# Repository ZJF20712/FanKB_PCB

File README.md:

# FanKB_PCB
The PCB project for FanKB
  Designed by KiCad.
    This is the third version,the next version I'd like to change MCU to stm32(software use Chibios), or make MDBT40 BT module on board to reduce the price of this keyboard.

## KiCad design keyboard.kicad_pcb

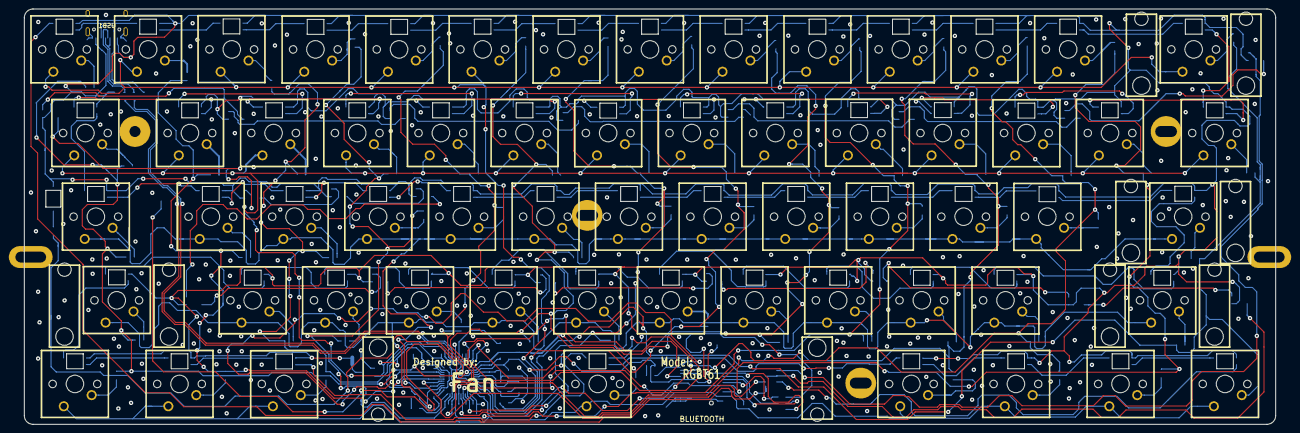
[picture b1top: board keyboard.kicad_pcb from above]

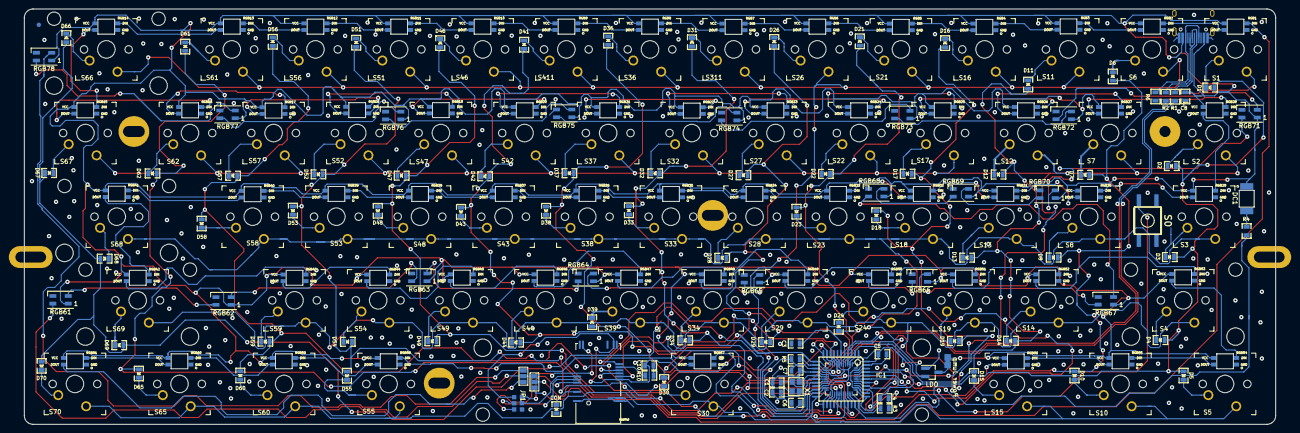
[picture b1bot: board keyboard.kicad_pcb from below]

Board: 2 copper layers, 285.0 x 94.6 mm, 245 parts (168 on the bottom side), 186 nets.

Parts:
BLUETOOTH: MDBT40; MDBT40_F
C1, C2: 22p; 0805C
C3, C8, C10: 1u; 0805C
C4, C5, C6, C7: 100n; 0805C
CON: LED; 0805D
D1, D2, D3, D4, D5, D6, D7, D8, D10, D11, D12, D13, D14, D15, D16, D17, D18, D19, D21, D22, D23, D24, D26, D27, D28, D29, D30, D31, D32, D33, D34, D36, D37, D38, D39, D41, D42, D43, D44, D46, D47, D48, D49, D51, D52, D53, D54, D55, D56, D57, D58, D59, D60, D61, D62, D65, D66, D67, D68, D69, D70: 1N4148; 0805D
DC1: LED; 3528_LED
FID: FIDUCIAL
HOLE: VAL**; PKRHSL
HOLE#2: VAL**; PKRHSL
HOLE#3, HOLE#4, HOLE#5: VAL**; PKRH
HOLE#6: VAL**; PKRHC
IC1: ATMEGA32U4; TQFP44
JP1, JP2: JUMPER3; SolderJumper-3_P1.3mm_Open_Pad1.0x1.5mm_NumberLabels
LDO: 2N7002; SOT-23_Handsoldering
MXST: VAL**; MXST
MXST#2, MXST#3, MXST#4, MXST#5, MXST#6, MXST#7, MXST#8, MXST#9, MXST#10: VAL**; MXST
P2: CONN_3X2; Jumper-UserFriendly
R1, R2: 22; 0805R
R3, R5: 10k; 0805R
R4: 300; 0805R
R6: 5.1K; 0805R
R10: 10K; 0805R
RGB1, RGB2, RGB3, RGB4, RGB5, RGB6, RGB7, RGB8, RGB9, RGB10, RGB11, RGB12, RGB13, RGB14, RGB15, RGB16, RGB17, RGB18, RGB19, RGB20, RGB21, RGB22, RGB23, RGB24, RGB25, RGB26, RGB27, RGB28, RGB29, RGB30, RGB31, RGB32, RGB33, RGB34, RGB35, RGB36, RGB37, RGB38, RGB39, RGB40, RGB41, RGB42, RGB43, RGB44, RGB45, RGB46, RGB47, RGB48, RGB49, RGB50, RGB51, RGB52, RGB53, RGB54, RGB55, RGB56, RGB57, RGB58, RGB59, RGB60, RGB81: WS2812B; WS2812-3528-with-sik
RGB61, RGB62, RGB63, RGB64, RGB65, RGB66, RGB67, RGB68, RGB69, RGB70, RGB71, RGB72, RGB73, RGB74, RGB75, RGB76, RGB77, RGB78: WS2812B; LED_SK6812MINI_PLCC4_3.5x3.5mm_P1.75mm
S0: DTSM-6; KSEM31GLFS
S1, S2, S3, S4, S5, S6, S7, S8, S10, S11, S12, S13, S14, S15, S16, S17, S18, S19, S21, S22, S23, S24, S26, S27, S28, S29, S30, S32, S33, S34, S36, S37, S38, S39, S42, S43, S44, S46, S47, S48, S49, S51, S52, S53, S54, S55, S56, S57, S58, S59, S60, S61, S62, S65, S66, S67, S68, S69, S70, S311, S411: MX1A; MX
USB1: HRO-TYPE-C-31-M-12; HRO-TYPE-C-31-M-12-HandSoldering
X1: ASX3F; 4-SMD

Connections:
/CONed: BLUETOOTH.39, CON.1
/D+: IC1.4, R2.1
/D-: IC1.3, R1.1
/DFU: BLUETOOTH.24, P2.5
/DIN_D: JP1.1, JP2.2, RGB61.4
/DIN_M: JP1.3, RGB1.4
/DIO_RST: BLUETOOTH.35, P2.3
/DOUT_D: JP2.1, RGB78.2
/DOUT_M: JP2.3, RGB81.2
/FACRST: BLUETOOTH.34, P2.4
/MISO: BLUETOOTH.5, IC1.11
/MOSI: BLUETOOTH.6, IC1.10
/SCK: BLUETOOTH.4, IC1.9
/SWCLK: BLUETOOTH.36, P2.2
/WS2812: IC1.38, JP1.2
/caps: IC1.8, R4.2
/col1: D1.1, D2.1, D3.1, D4.1, D5.1, IC1.41
/col2: D6.1, D7.1, D8.1, D10.1, IC1.40
/col3: D11.1, D12.1, D13.1, D14.1, D15.1, IC1.1
/col4: D16.1, D17.1, D18.1, D19.1, IC1.32
/col5: D21.1, D22.1, D23.1, D24.1, IC1.31
/col6: D26.1, D27.1, D28.1, D29.1, D30.1, IC1.30
/col7: D31.1, D32.1, D33.1, D34.1, IC1.25
/col8: D36.1, D37.1, D38.1, D39.1, IC1.20
/col9: D41.1, D42.1, D43.1, D44.1, IC1.12
/col10: D46.1, D47.1, D48.1, D49.1, IC1.29
/col11: D51.1, D52.1, D53.1, D54.1, D55.1, IC1.28
/col12: D56.1, D57.1, D58.1, D59.1, D60.1, IC1.27
/col13: D61.1, D62.1, D65.1, IC1.26
/col14: D66.1, D67.1, D68.1, D69.1, D70.1, IC1.21
/row1: IC1.18, S1.1, S6.1, S11.1, S16.1, S21.1, S26.1, S36.1, S46.1, S51.1, S56.1, S61.1, S66.1, S311.1, S411.1
/row2: IC1.19, S2.1, S7.1, S12.1, S17.1, S22.1, S27.1, S32.1, S37.1, S42.1, S47.1, S52.1, S57.1, S62.1, S67.1
/row3: IC1.37, S3.1, S8.1, S13.1, S18.1, S23.1, S28.1, S33.1, S38.1, S43.1, S48.1, S53.1, S58.1, S68.1
/row4: IC1.36, S4.1, S14.1, S19.1, S24.1, S29.1, S34.1, S39.1, S44.1, S49.1, S54.1, S59.1, S69.1
/row5: IC1.22, S5.1, S10.1, S15.1, S30.1, S55.1, S60.1, S65.1, S70.1
GND: BLUETOOTH.1, BLUETOOTH.2, BLUETOOTH.13, BLUETOOTH.16, BLUETOOTH.25, BLUETOOTH.42, C1.2, C2.2, C3.2, C4.2, C5.2, C6.2, C7.2, C8.2, C10.1, CON.2, IC1.5, IC1.15, IC1.23, IC1.35, IC1.43, LDO.1, P2.6, R3.2, R6.1, R10.1, RGB1.3, RGB2.3, RGB3.3, RGB4.3, RGB5.3, RGB6.3, RGB7.3, RGB8.3, RGB9.3, RGB10.3, RGB11.3, RGB12.3, RGB13.3, RGB14.3, RGB15.3, RGB16.3, RGB17.3, RGB18.3, RGB19.3, RGB20.3, RGB21.3, RGB22.3, RGB23.3, RGB24.3, RGB25.3, RGB26.3, RGB27.3, RGB28.3, RGB29.3, RGB30.3, RGB31.3, RGB32.3, RGB33.3, RGB34.3, RGB35.3, RGB36.3, RGB37.3, RGB38.3, RGB39.3, RGB40.3, RGB41.3, RGB42.3, RGB43.3, RGB44.3, RGB45.3, RGB46.3, RGB47.3, RGB48.3, RGB49.3, RGB50.3, RGB51.3, RGB52.3, RGB53.3, RGB54.3, RGB55.3, RGB56.3, RGB57.3, RGB58.3, RGB59.3, RGB60.3, RGB61.3, RGB62.3, RGB63.3, RGB64.3, RGB65.3, RGB66.3, RGB67.3, RGB68.3, RGB69.3, RGB70.3, RGB71.3, RGB72.3, RGB73.3, RGB74.3, RGB75.3, RGB76.3, RGB77.3, RGB78.3, RGB81.3, S0.1, USB1.1, USB1.12, USB1.13, X1.2, X1.4
unnamed: C1.1, IC1.16, X1.1
unnamed: C2.1, IC1.17, X1.3
unnamed: C3.1, IC1.6
unnamed: D1.2, S1.2
unnamed: D2.2, S2.2
unnamed: D3.2, S3.2
unnamed: D4.2, S4.2
unnamed: D5.2, S5.2
unnamed: D6.2, S6.2
unnamed: D7.2, S7.2
unnamed: D8.2, S8.2
unnamed: D10.2, S10.2
unnamed: D11.2, S11.2
unnamed: D12.2, S12.2
unnamed: D13.2, S13.2
unnamed: D14.2, S14.2
unnamed: D15.2, S15.2
unnamed: D16.2, S16.2
unnamed: D17.2, S17.2
unnamed: D18.2, S18.2
unnamed: D19.2, S19.2
unnamed: D21.2, S21.2
unnamed: D22.2, S22.2
unnamed: D23.2, S23.2
unnamed: D24.2, S24.2
unnamed: D26.2, S26.2
unnamed: D27.2, S27.2
unnamed: D28.2, S28.2
unnamed: D29.2, S29.2
unnamed: D30.2, S30.2
unnamed: D31.2, S311.2
unnamed: D32.2, S32.2
unnamed: D33.2, S33.2
unnamed: D34.2, S34.2
unnamed: D36.2, S36.2
unnamed: D37.2, S37.2
unnamed: D38.2, S38.2
unnamed: D39.2, S39.2
unnamed: D41.2, S411.2
unnamed: D42.2, S42.2
unnamed: D43.2, S43.2
unnamed: D44.2, S44.2
unnamed: D46.2, S46.2
unnamed: D47.2, S47.2
unnamed: D48.2, S48.2
unnamed: D49.2, S49.2
unnamed: D51.2, S51.2
unnamed: D52.2, S52.2
unnamed: D53.2, S53.2
unnamed: D54.2, S54.2
unnamed: D55.2, S55.2
unnamed: D56.2, S56.2
unnamed: D57.2, S57.2
unnamed: D58.2, S58.2
unnamed: D59.2, S59.2
unnamed: D60.2, S60.2
unnamed: D61.2, S61.2
unnamed: D62.2, S62.2
unnamed: D65.2, S65.2
unnamed: D66.2, S66.2
unnamed: D67.2, S67.2
unnamed: D68.2, S68.2
unnamed: D69.2, S69.2
unnamed: D70.2, S70.2
unnamed: DC1.2, R4.1
unnamed: IC1.13, R5.2, S0.3
unnamed: IC1.33, R3.1
unnamed: BLUETOOTH.8, IC1.39
unnamed: R1.2, USB1.5, USB1.7
unnamed: R2.2, USB1.6, USB1.8
unnamed: R6.2, USB1.4, USB1.10
unnamed: BLUETOOTH.7, R10.2
unnamed: RGB1.2, RGB2.4
unnamed: RGB2.2, RGB3.4
unnamed: RGB3.2, RGB4.4
unnamed: RGB4.2, RGB5.4
unnamed: RGB5.2, RGB6.4
unnamed: RGB6.2, RGB7.4
unnamed: RGB7.2, RGB8.4
unnamed: RGB8.2, RGB9.4
unnamed: RGB10.2, RGB11.4
unnamed: RGB9.2, RGB10.4
unnamed: RGB11.2, RGB12.4
unnamed: RGB12.2, RGB13.4
unnamed: RGB13.2, RGB14.4
unnamed: RGB14.2, RGB15.4
unnamed: RGB15.2, RGB16.4
unnamed: RGB16.2, RGB17.4
unnamed: RGB17.2, RGB18.4
unnamed: RGB18.2, RGB19.4
unnamed: RGB19.2, RGB20.4
unnamed: RGB20.2, RGB21.4
unnamed: RGB21.2, RGB22.4
unnamed: RGB22.2, RGB23.4
unnamed: RGB23.2, RGB24.4
unnamed: RGB24.2, RGB25.4
unnamed: RGB25.2, RGB26.4
unnamed: RGB26.2, RGB27.4
unnamed: RGB27.2, RGB28.4
unnamed: RGB28.2, RGB29.4
unnamed: RGB29.2, RGB30.4
unnamed: RGB30.2, RGB31.4
unnamed: RGB31.2, RGB32.4
unnamed: RGB32.2, RGB33.4
unnamed: RGB33.2, RGB34.4
unnamed: RGB34.2, RGB35.4
unnamed: RGB35.2, RGB36.4
unnamed: RGB36.2, RGB37.4
unnamed: RGB37.2, RGB38.4
unnamed: RGB38.2, RGB39.4
unnamed: RGB39.2, RGB40.4
unnamed: RGB40.2, RGB41.4
unnamed: RGB41.2, RGB42.4
unnamed: RGB42.2, RGB43.4
unnamed: RGB43.2, RGB44.4
unnamed: RGB44.2, RGB45.4
unnamed: RGB45.2, RGB46.4
unnamed: RGB46.2, RGB47.4
unnamed: RGB47.2, RGB48.4
unnamed: RGB48.2, RGB49.4
unnamed: RGB49.2, RGB50.4
unnamed: RGB50.2, RGB51.4
unnamed: RGB51.2, RGB52.4
unnamed: RGB52.2, RGB53.4
unnamed: RGB53.2, RGB54.4
unnamed: RGB54.2, RGB55.4
unnamed: RGB55.2, RGB56.4
unnamed: RGB56.2, RGB57.4
unnamed: RGB57.2, RGB58.4
unnamed: RGB58.2, RGB59.4
unnamed: RGB59.2, RGB60.4
unnamed: RGB60.2, RGB81.4
unnamed: RGB61.2, RGB62.4
unnamed: RGB62.2, RGB63.4
unnamed: RGB63.2, RGB64.4
unnamed: RGB64.2, RGB65.4
unnamed: RGB65.2, RGB66.4
unnamed: RGB66.2, RGB67.4
unnamed: RGB67.2, RGB68.4
unnamed: RGB68.2, RGB69.4
unnamed: RGB69.2, RGB70.4
unnamed: RGB70.2, RGB71.4
unnamed: RGB71.2, RGB72.4
unnamed: RGB72.2, RGB73.4
unnamed: RGB73.2, RGB74.4
unnamed: RGB74.2, RGB75.4
unnamed: RGB75.2, RGB76.4
unnamed: RGB76.2, RGB77.4
unnamed: RGB77.2, RGB78.4
VCC: BLUETOOTH.3, BLUETOOTH.14, C4.1, C5.1, C6.1, C7.1, C8.1, C10.2, DC1.1, IC1.2, IC1.7, IC1.14, IC1.24, IC1.34, IC1.44, LDO.2, LDO.3, P2.1, R5.1, RGB1.1, RGB2.1, RGB3.1, RGB4.1, RGB5.1, RGB6.1, RGB7.1, RGB8.1, RGB9.1, RGB10.1, RGB11.1, RGB12.1, RGB13.1, RGB14.1, RGB15.1, RGB16.1, RGB17.1, RGB18.1, RGB19.1, RGB20.1, RGB21.1, RGB22.1, RGB23.1, RGB24.1, RGB25.1, RGB26.1, RGB27.1, RGB28.1, RGB29.1, RGB30.1, RGB31.1, RGB32.1, RGB33.1, RGB34.1, RGB35.1, RGB36.1, RGB37.1, RGB38.1, RGB39.1, RGB40.1, RGB41.1, RGB42.1, RGB43.1, RGB44.1, RGB45.1, RGB46.1, RGB47.1, RGB48.1, RGB49.1, RGB50.1, RGB51.1, RGB52.1, RGB53.1, RGB54.1, RGB55.1, RGB56.1, RGB57.1, RGB58.1, RGB59.1, RGB60.1, RGB61.1, RGB62.1, RGB63.1, RGB64.1, RGB65.1, RGB66.1, RGB67.1, RGB68.1, RGB69.1, RGB70.1, RGB71.1, RGB72.1, RGB73.1, RGB74.1, RGB75.1, RGB76.1, RGB77.1, RGB78.1, RGB81.1, USB1.2, USB1.11

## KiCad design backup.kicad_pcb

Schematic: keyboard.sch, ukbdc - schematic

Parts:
BAT1: CONN_2; PinHeader_1x02_P2.54mm_Vertical
C1, C7, C9, C10, C12, C13: 1u; 0805C
C2, C3, C5, C6: 100n; R_0603_1608Metric
C4, C8: 22p; R_0603_1608Metric
C11: 104; R_0603_1608Metric
D1: CHG; 0805D
D2: CHDONE; 0805D
D3: LED; 0805D
IC1: ATMEGA32U4; QFN_32U4
JP1: Power; solder_jumper
Q1: 2N7002; SOT-23_Handsoldering
Q2: Q_PMOS_GDS; SOT-23_Handsoldering
R1: 5.1K; R_0603_1608Metric
R2, R3: 22; R_0603_1608Metric
R4, R5, R7, R8: 10k; R_0603_1608Metric
R6: 1k; R_0603_1608Metric
SW1: JUMPER; SW_SPST_CK_RS282G05A3
SW2: CONN_3; SW_Slide_1P2T_CK_OS102011MS2Q
U1: TP4056; SOIC-8_3.9x4.9mm_Pitch1.27mm
U2: MDBT40; MDBT40_UART
USB1: HRO-TYPE-C-31-M-12; HRO-TYPE-C-31-M-12-HandSoldering
X1: ASX3F; 4-SMD

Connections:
/BAT_V: R7.2, R8.1, U2.22
/BT_EN: IC1.11 ((PDO/PCINT3/MISO)PB3), Q2.1
/BT_RX: IC1.21 ((TXD1/INT3)PD3), U2.29
/BT_TX: IC1.20 ((RXD1/INT2)PD2), U2.27
/CONed: D3.1 (A), U2.39
/D+: IC1.4 (D+), R3.1
/D-: IC1.3 (D-), R2.1
/DFU: U2.24; also elsewhere on the board
/DIO_RST: U2.35; also elsewhere on the board
/FACRST: U2.34; also elsewhere on the board
/PWDN: IC1.10 ((PDI/PCINT2/MOSI)PB2); also elsewhere on the board
/SCL: IC1.18 ((OC0B/SCL/INT0)PD0); also elsewhere on the board
/SDA: IC1.19 ((SDA/INT1)PD1); also elsewhere on the board
/SWCLK: U2.36; also elsewhere on the board
/col1: IC1.41 ((ADC0)PF0); also elsewhere on the board
/col2: IC1.40 ((ADC1)PF1); also elsewhere on the board
/col3: IC1.1 ((INT6/AIN0)PE6); also elsewhere on the board
/col4: IC1.32 ((ICP3/CLK0/OC4A)PC7); also elsewhere on the board
/col5: IC1.31 ((OC3A/~OC4A~)PC6); also elsewhere on the board
/col6: IC1.30 ((PCINT6/OC1B/OC4B/ADC13)PB6); also elsewhere on the board
/col7: IC1.25 ((ICP1/ADC8)PD4); also elsewhere on the board
/col8: IC1.9 ((PCINT1/SCLK)PB1); also elsewhere on the board
/col9: IC1.12 ((PCINT7/OC0A/OC1C/~RTS~)PB7); also elsewhere on the board
/col10: IC1.29 ((PCINT5/OC1A/~OC4B~/ADC12)PB5); also elsewhere on the board
/col11: IC1.28 ((PCINT4/ADC11)PB4); also elsewhere on the board
/col12: IC1.27 ((T0/OC4D/ADC10)PD7); also elsewhere on the board
/col13: IC1.26 ((T1/~OC4D~/ADC9)PD6); also elsewhere on the board
/col14: IC1.8 ((SS/PCINT0)PB0); also elsewhere on the board
/row1: IC1.39 ((ADC4/TCK)PF4); also elsewhere on the board
/row2: IC1.38 ((ADC5/TMS)PF5); also elsewhere on the board
/row3: IC1.37 ((ADC6/TDO)PF6); also elsewhere on the board
/row4: IC1.36 ((ADC7/TDI)PF7); also elsewhere on the board
/row5: IC1.22 ((XCK1/~CTS~)PD5); also elsewhere on the board
GND: BAT1.2, C1.2, C2.2, C3.2, C4.2, C5.2, C6.2, C7.2, C8.2, C9.2, C10.2, C11.1, C12.2, C13.2, D3.2 (K), IC1.5 (UGnd), IC1.15 (GND), IC1.23 (GND), IC1.35 (GND), IC1.43 (GND), Q1.1, R1.1, R5.2, R6.2, R8.2, SW1.1, U1.1, U1.3, U2.1, U2.2, U2.13, U2.16, U2.25, U2.42, USB1.1, USB1.12, USB1.13, X1.2 (GND), X1.4 (GND); also elsewhere on the board
unnamed: SW2.3, U1.5
unnamed: C4.1, IC1.16 (XTAL2), X1.1
unnamed: C7.1, IC1.6 (Ucap)
unnamed: C8.1, IC1.17 (XTAL1), X1.3 (2)
unnamed 67: C11.2, Q2.3, U2.3, U2.14; also elsewhere on the board
unnamed: D1.2 (K), U1.7
unnamed: D2.2 (K), U1.6
unnamed: IC1.13 (~RESET~), R4.2, SW1.2
unnamed: IC1.33 ((~HWB~)PE2), R5.1
unnamed: R1.2, USB1.4, USB1.10
unnamed: R2.2, USB1.5, USB1.7
unnamed: R3.2, USB1.6, USB1.8
unnamed: R6.1, U1.2
VCC: C1.1, C2.1, C3.1, C5.1, C6.1, C13.1, IC1.2 (UVcc), IC1.14 (VCC), IC1.24 (AVCC), IC1.34 (VCC), IC1.44 (AVCC), Q1.2, Q2.2, R4.1

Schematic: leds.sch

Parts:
C15, C16, C17: 104; R_0603_1608Metric
R9, R10, R13, R14: 10k; R_0603_1608Metric
R12: 20k; R_0603_1608Metric
RGB1, RGB2, RGB3, RGB4, RGB5, RGB6, RGB7, RGB8, RGB9, RGB10, RGB11, RGB12, RGB13, RGB14, RGB15, RGB16, RGB17, RGB18, RGB19, RGB20, RGB21, RGB22, RGB23, RGB24, RGB25, RGB26, RGB27, RGB28, RGB29, RGB30, RGB31, RGB32, RGB33, RGB34, RGB35, RGB36, RGB37, RGB38, RGB39, RGB40, RGB41, RGB42, RGB43, RGB44, RGB45, RGB46, RGB47, RGB48, RGB49, RGB50, RGB51, RGB52, RGB53, RGB54, RGB55, RGB56, RGB57, RGB58, RGB59, RGB60, RGB61: LED_ARGB; RGB-3528-with-sik
U3: IS31FL3733; QFN-48-1EP_6x6mm_P0.4mm_EP4.2x4.2mm

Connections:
/PWDN: R14.2, U3.46; also elsewhere on the board
/SCL: R9.1, U3.42; also elsewhere on the board
/SDA: R10.1, U3.41; also elsewhere on the board
/leds/CS1: RGB1.1, RGB28.1, RGB29.1, RGB53.1, U3.16
/leds/CS2: RGB2.1, RGB27.1, RGB30.1, RGB52.1, U3.17
/leds/CS3: RGB3.1, RGB26.1, RGB31.1, RGB51.1, U3.18
/leds/CS4: RGB4.1, RGB25.1, RGB32.1, RGB50.1, U3.19
/leds/CS5: RGB5.1, RGB24.1, RGB33.1, RGB49.1, U3.21
/leds/CS6: RGB6.1, RGB23.1, RGB34.1, RGB48.1, U3.22
/leds/CS7: RGB7.1, RGB22.1, RGB35.1, RGB47.1, U3.23
/leds/CS8: RGB8.1, RGB21.1, RGB36.1, RGB46.1, U3.24
/leds/CS9: RGB9.1, RGB20.1, RGB37.1, RGB45.1, U3.25
/leds/CS10: RGB10.1, RGB19.1, RGB38.1, RGB44.1, U3.26
/leds/CS11: RGB11.1, RGB18.1, RGB39.1, RGB43.1, U3.27
/leds/CS12: RGB12.1, RGB17.1, RGB40.1, RGB42.1, U3.28
/leds/CS13: RGB13.1, RGB16.1, RGB41.1, RGB61.1, U3.30
/leds/CS14: RGB14.1, RGB15.1, RGB60.1, U3.31
/leds/CS15: RGB57.1, RGB59.1, U3.32
/leds/CS16: RGB54.1, RGB55.1, RGB56.1, RGB58.1, U3.33
/leds/I2CRST: R13.2, U3.47
/leds/SW1: RGB1.4, RGB2.4, RGB3.4, RGB4.4, RGB5.4, RGB6.4, RGB7.4, RGB8.4, RGB9.4, RGB10.4, RGB11.4, RGB12.4, RGB13.4, RGB14.4, RGB54.4, U3.2
/leds/SW2: RGB1.3, RGB2.3, RGB3.3, RGB4.3, RGB5.3, RGB6.3, RGB7.3, RGB8.3, RGB9.3, RGB10.3, RGB11.3, RGB12.3, RGB13.3, RGB14.3, RGB54.3, U3.3
/leds/SW3: RGB1.2, RGB2.2, RGB3.2, RGB4.2, RGB5.2, RGB6.2, RGB7.2, RGB8.2, RGB9.2, RGB10.2, RGB11.2, RGB12.2, RGB13.2, RGB14.2, RGB54.2, U3.4
/leds/SW4: RGB15.4, RGB16.4, RGB17.4, RGB18.4, RGB19.4, RGB20.4, RGB21.4, RGB22.4, RGB23.4, RGB24.4, RGB25.4, RGB26.4, RGB27.4, RGB28.4, RGB55.4, U3.6
/leds/SW5: RGB15.3, RGB16.3, RGB17.3, RGB18.3, RGB19.3, RGB20.3, RGB21.3, RGB22.3, RGB23.3, RGB24.3, RGB25.3, RGB26.3, RGB27.3, RGB28.3, RGB55.3, U3.7
/leds/SW6: RGB15.2, RGB16.2, RGB17.2, RGB18.2, RGB19.2, RGB20.2, RGB21.2, RGB22.2, RGB23.2, RGB24.2, RGB25.2, RGB26.2, RGB27.2, RGB28.2, RGB55.2, U3.8
/leds/SW7: RGB29.4, RGB30.4, RGB31.4, RGB32.4, RGB33.4, RGB34.4, RGB35.4, RGB36.4, RGB37.4, RGB38.4, RGB39.4, RGB40.4, RGB41.4, RGB56.4, RGB57.4, U3.9
/leds/SW8: RGB29.3, RGB30.3, RGB31.3, RGB32.3, RGB33.3, RGB34.3, RGB35.3, RGB36.3, RGB37.3, RGB38.3, RGB39.3, RGB40.3, RGB41.3, RGB56.3, RGB57.3, U3.10
/leds/SW9: RGB29.2, RGB30.2, RGB31.2, RGB32.2, RGB33.2, RGB34.2, RGB35.2, RGB36.2, RGB37.2, RGB38.2, RGB39.2, RGB40.2, RGB41.2, RGB56.2, RGB57.2, U3.11
/leds/SW10: RGB42.4, RGB43.4, RGB44.4, RGB45.4, RGB46.4, RGB47.4, RGB48.4, RGB49.4, RGB50.4, RGB51.4, RGB52.4, RGB53.4, RGB58.4, RGB59.4, RGB60.4, RGB61.4, U3.13
/leds/SW11: RGB42.3, RGB43.3, RGB44.3, RGB45.3, RGB46.3, RGB47.3, RGB48.3, RGB49.3, RGB50.3, RGB51.3, RGB52.3, RGB53.3, RGB58.3, RGB59.3, RGB60.3, RGB61.3, U3.14
/leds/SW12: RGB42.2, RGB43.2, RGB44.2, RGB45.2, RGB46.2, RGB47.2, RGB48.2, RGB49.2, RGB50.2, RGB51.2, RGB52.2, RGB53.2, RGB58.2, RGB59.2, RGB60.2, RGB61.2, U3.15
GND: C15.2, C16.2, C17.2, R12.2, R13.1, R14.1, U3.5, U3.12, U3.34, U3.43, U3.44, U3.48, U3.49; also elsewhere on the board
unnamed 68: R12.1, U3.35; also elsewhere on the board

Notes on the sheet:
ESC
backspace
TAB
CAPSLOCK
ENTER
LSHIFT
RSHIFT
RCTRL
RTEXT
RALT
SPACE
LCTRL
LGUI
LALT

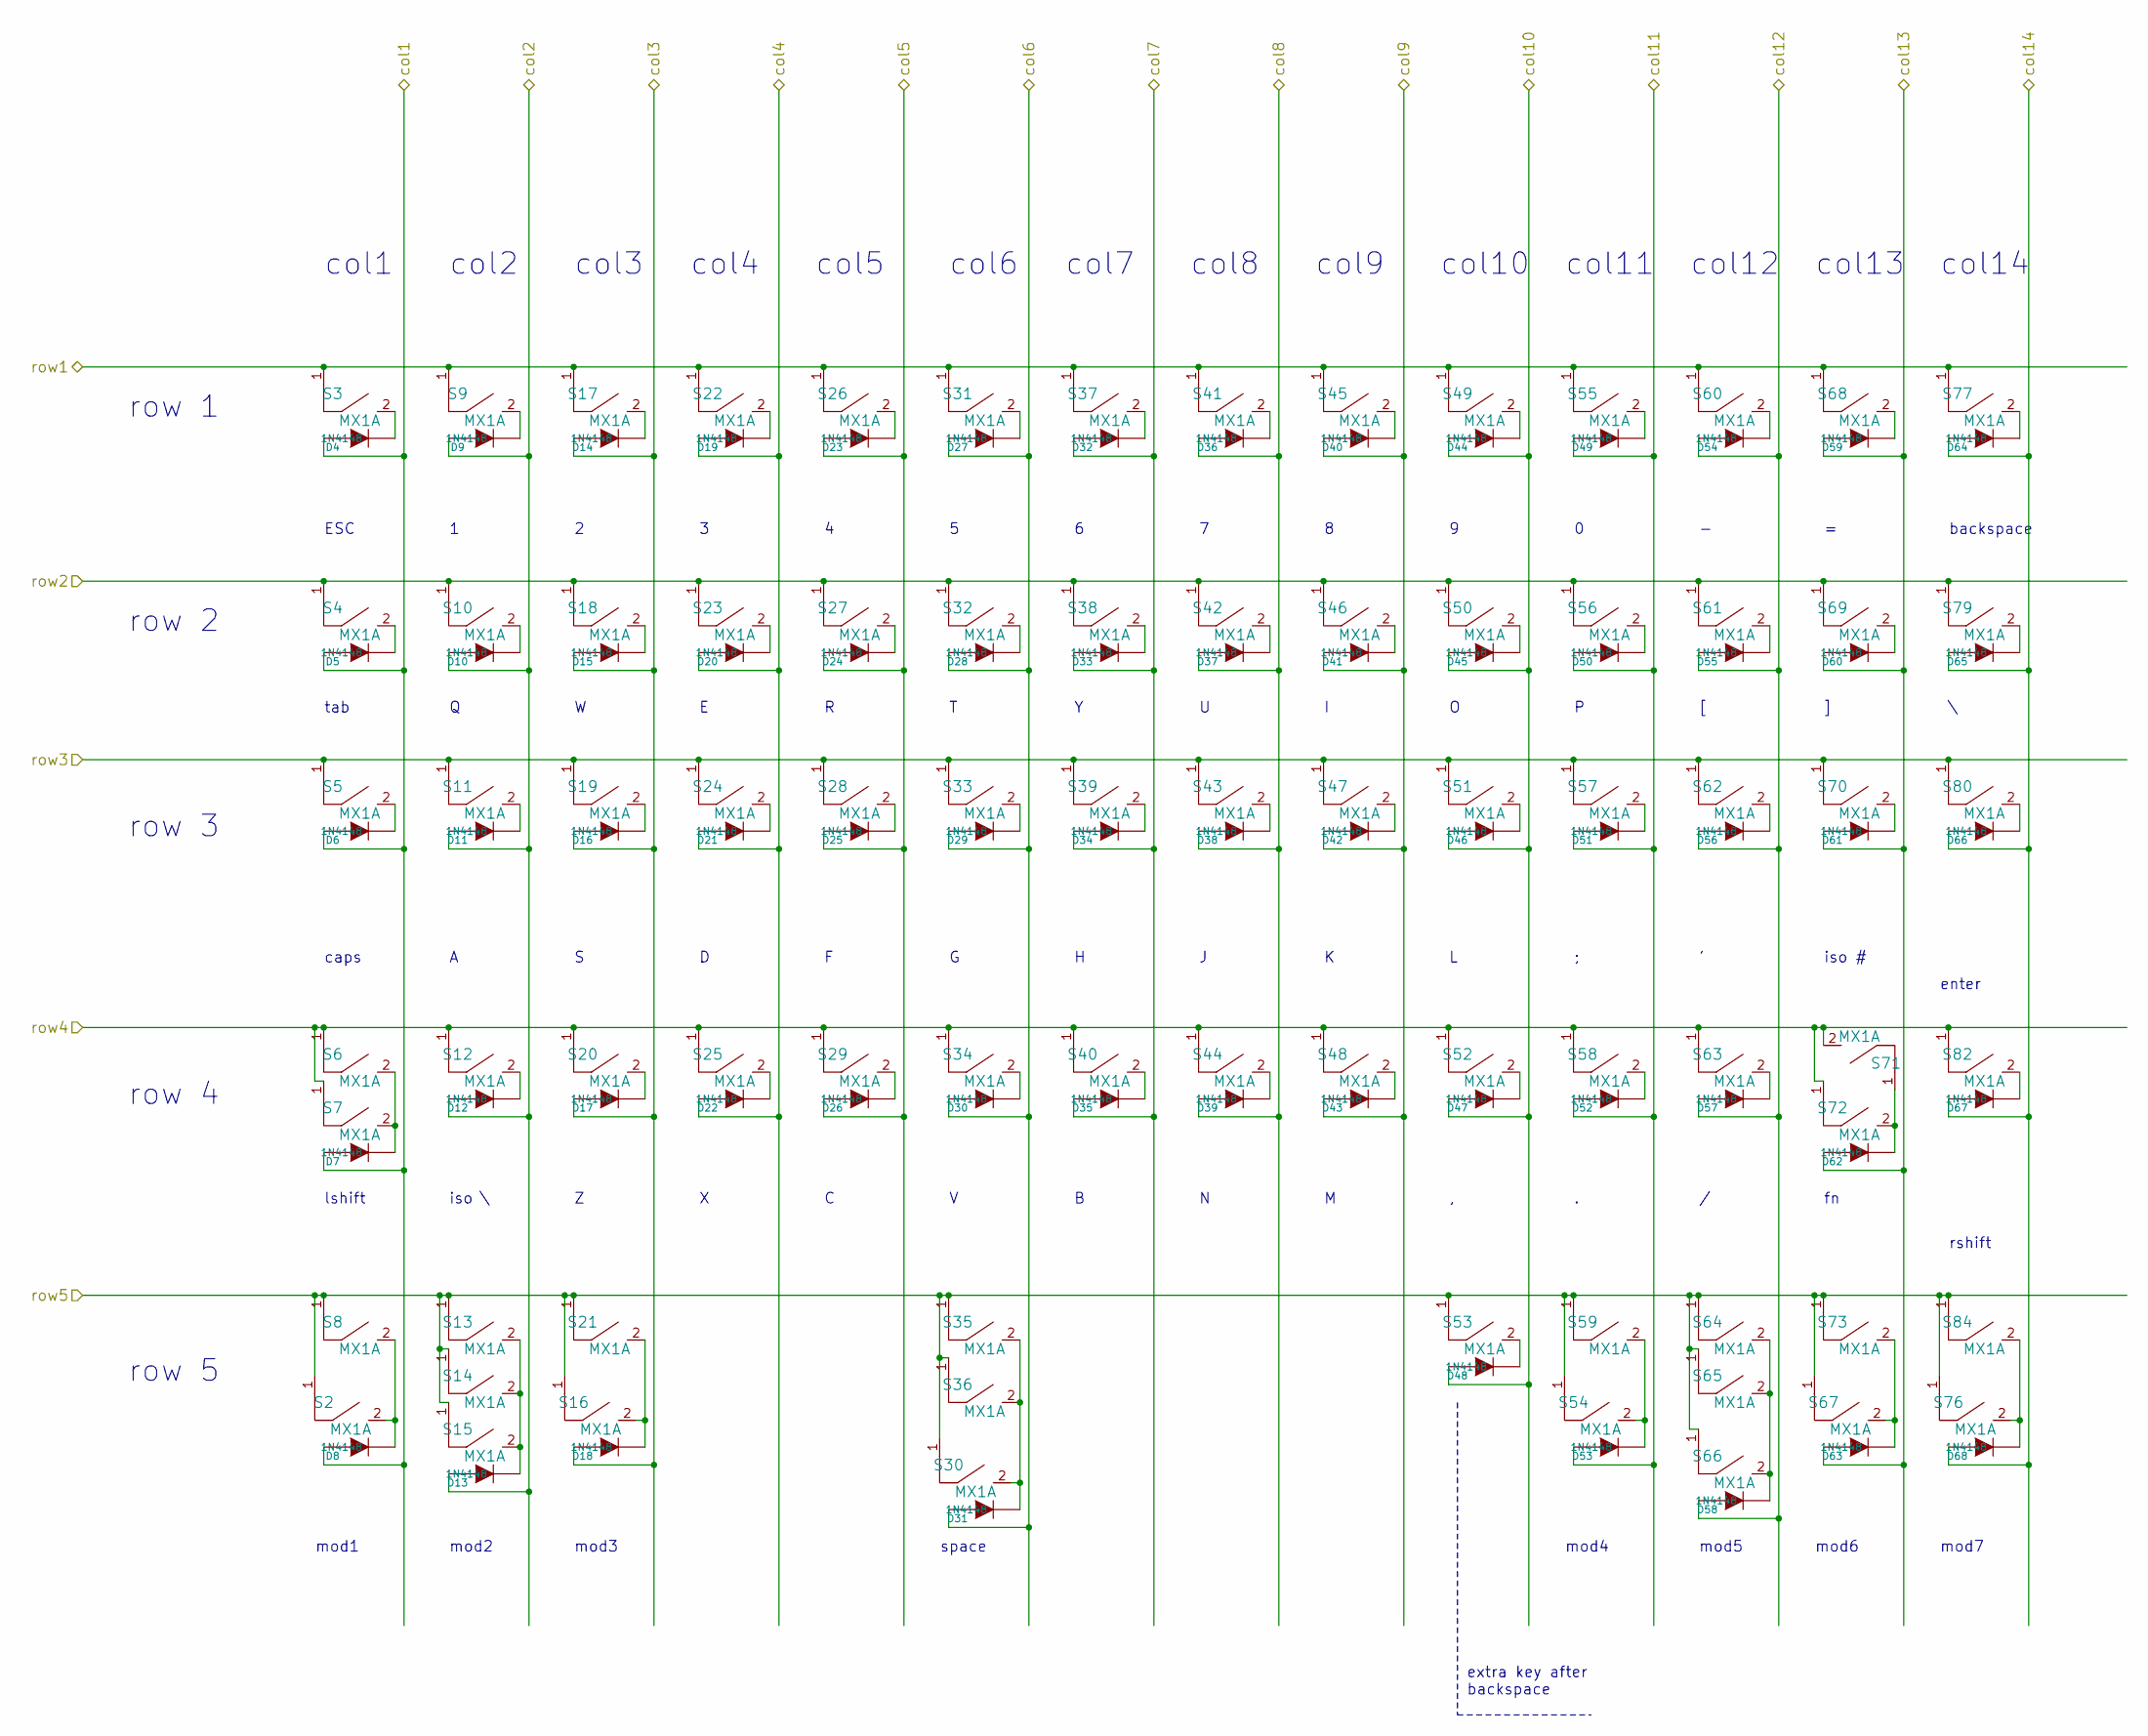
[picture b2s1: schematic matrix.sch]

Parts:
D4, D5, D6, D7, D8, D9, D10, D11, D12, D13, D14, D15, D16, D17, D18, D19, D20, D21, D22, D23, D24, D25, D26, D27, D28, D29, D30, D31, D32, D33, D34, D35, D36, D37, D38, D39, D40, D41, D42, D43, D44, D45, D46, D47, D48, D49, D50, D51, D52, D53, D54, D55, D56, D57, D58, D59, D60, D61, D62, D63, D64, D65, D66, D67, D68: 1N4148; 0805D
S2, S3, S4, S5, S6, S7, S8, S9, S10, S11, S12, S13, S14, S15, S16, S17, S18, S19, S20, S21, S22, S23, S24, S25, S26, S27, S28, S29, S30, S31, S32, S33, S34, S35, S36, S37, S38, S39, S40, S41, S42, S43, S44, S45, S46, S47, S48, S49, S50, S51, S52, S53, S54, S55, S56, S57, S58, S59, S60, S61, S62, S63, S64, S65, S66, S67, S68, S69, S70, S71, S72, S73, S76, S77, S79, S80, S82, S84: MX1A; MX

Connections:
/col1: D4.1 (A), D5.1 (A), D6.1 (A), D7.1 (A), D8.1 (A); also elsewhere on the board
/col2: D9.1 (A), D10.1 (A), D11.1 (A), D12.1 (A), D13.1 (A); also elsewhere on the board
/col3: D14.1 (A), D15.1 (A), D16.1 (A), D17.1 (A), D18.1 (A); also elsewhere on the board
/col4: D19.1 (A), D20.1 (A), D21.1 (A), D22.1 (A); also elsewhere on the board
/col5: D23.1 (A), D24.1 (A), D25.1 (A), D26.1 (A); also elsewhere on the board
/col6: D27.1 (A), D28.1 (A), D29.1 (A), D30.1 (A), D31.1 (A); also elsewhere on the board
/col7: D32.1 (A), D33.1 (A), D34.1 (A), D35.1 (A); also elsewhere on the board
/col8: D36.1 (A), D37.1 (A), D38.1 (A), D39.1 (A); also elsewhere on the board
/col9: D40.1 (A), D41.1 (A), D42.1 (A), D43.1 (A); also elsewhere on the board
/col10: D44.1 (A), D45.1 (A), D46.1 (A), D47.1 (A), D48.1 (A); also elsewhere on the board
/col11: D49.1 (A), D50.1 (A), D51.1 (A), D52.1 (A), D53.1 (A); also elsewhere on the board
/col12: D54.1 (A), D55.1 (A), D56.1 (A), D57.1 (A), D58.1 (A); also elsewhere on the board
/col13: D59.1 (A), D60.1 (A), D61.1 (A), D62.1 (A), D63.1 (A); also elsewhere on the board
/col14: D64.1 (A), D65.1 (A), D66.1 (A), D67.1 (A), D68.1 (A); also elsewhere on the board
/row1: S3.1, S9.1, S17.1, S22.1, S26.1, S31.1, S37.1, S41.1, S45.1, S49.1, S55.1, S60.1, S68.1, S77.1; also elsewhere on the board
/row2: S4.1, S10.1, S18.1, S23.1, S27.1, S32.1, S38.1, S42.1, S46.1, S50.1, S56.1, S61.1, S69.1, S79.1; also elsewhere on the board
/row3: S5.1, S11.1, S19.1, S24.1, S28.1, S33.1, S39.1, S43.1, S47.1, S51.1, S57.1, S62.1, S70.1, S80.1; also elsewhere on the board
/row4: S6.1, S7.1, S12.1, S20.1, S25.1, S29.1, S34.1, S40.1, S44.1, S48.1, S52.1, S58.1, S63.1, S71.2, S72.1, S82.1; also elsewhere on the board
/row5: S2.1, S8.1, S13.1, S14.1, S15.1, S16.1, S21.1, S30.1, S35.1, S36.1, S53.1, S54.1, S59.1, S64.1, S65.1, S66.1, S67.1, S73.1, S76.1, S84.1; also elsewhere on the board
unnamed: D4.2 (K), S3.2
unnamed: D5.2 (K), S4.2
unnamed: D6.2 (K), S5.2
unnamed: D7.2 (K), S6.2, S7.2
unnamed: D8.2 (K), S2.2, S8.2
unnamed: D9.2 (K), S9.2
unnamed: D10.2 (K), S10.2
unnamed: D11.2 (K), S11.2
unnamed: D12.2 (K), S12.2
unnamed: D13.2 (K), S13.2, S14.2, S15.2
unnamed: D14.2 (K), S17.2
unnamed: D15.2 (K), S18.2
unnamed: D16.2 (K), S19.2
unnamed: D17.2 (K), S20.2
unnamed: D18.2 (K), S16.2, S21.2
unnamed: D19.2 (K), S22.2
unnamed: D20.2 (K), S23.2
unnamed: D21.2 (K), S24.2
unnamed: D22.2 (K), S25.2
unnamed: D23.2 (K), S26.2
unnamed: D24.2 (K), S27.2
unnamed: D25.2 (K), S28.2
unnamed: D26.2 (K), S29.2
unnamed: D27.2 (K), S31.2
unnamed: D28.2 (K), S32.2
unnamed: D29.2 (K), S33.2
unnamed: D30.2 (K), S34.2
unnamed: D31.2 (K), S30.2, S35.2, S36.2
unnamed: D32.2 (K), S37.2
unnamed: D33.2 (K), S38.2
unnamed: D34.2 (K), S39.2
unnamed: D35.2 (K), S40.2
unnamed: D36.2 (K), S41.2
unnamed: D37.2 (K), S42.2
unnamed: D38.2 (K), S43.2
unnamed: D39.2 (K), S44.2
unnamed: D40.2 (K), S45.2
unnamed: D41.2 (K), S46.2
unnamed: D42.2 (K), S47.2
unnamed: D43.2 (K), S48.2
unnamed: D44.2 (K), S49.2
unnamed: D45.2 (K), S50.2
unnamed: D46.2 (K), S51.2
unnamed: D47.2 (K), S52.2
unnamed: D48.2 (K), S53.2
unnamed: D49.2 (K), S55.2
unnamed: D50.2 (K), S56.2
unnamed: D51.2 (K), S57.2
unnamed: D52.2 (K), S58.2
unnamed: D53.2 (K), S54.2, S59.2
unnamed: D54.2 (K), S60.2
unnamed: D55.2 (K), S61.2
unnamed: D56.2 (K), S62.2
unnamed: D57.2 (K), S63.2
unnamed: D58.2 (K), S64.2, S65.2, S66.2
unnamed: D59.2 (K), S68.2
unnamed: D60.2 (K), S69.2
unnamed: D61.2 (K), S70.2
unnamed: D62.2 (K), S71.1, S72.2
unnamed: D63.2 (K), S67.2, S73.2
unnamed: D64.2 (K), S77.2
unnamed: D65.2 (K), S79.2
unnamed: D66.2 (K), S80.2
unnamed: D67.2 (K), S82.2
unnamed: D68.2 (K), S76.2, S84.2

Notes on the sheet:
row 1
row 2
row 3
row 4
row 5
col1
col2
col3
col4
col5
col6
col7
col9
col10
col11
col12
col13
col14
col8
ESC
backspace
tab
caps
iso #
enter
lshift
iso \
rshift
mod1
mod2
mod3
space
mod4
mod5
mod6
mod7
extra key after backspace

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
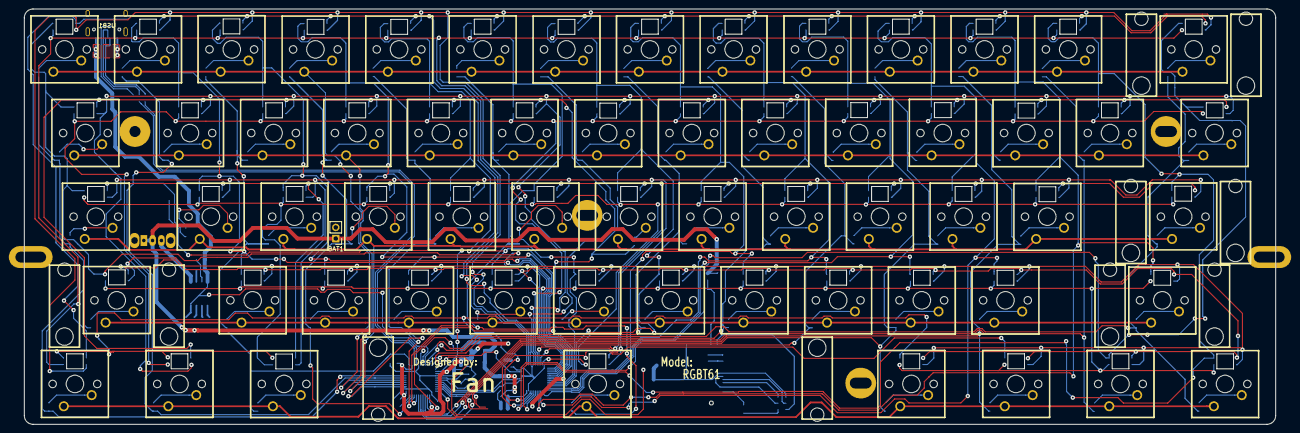
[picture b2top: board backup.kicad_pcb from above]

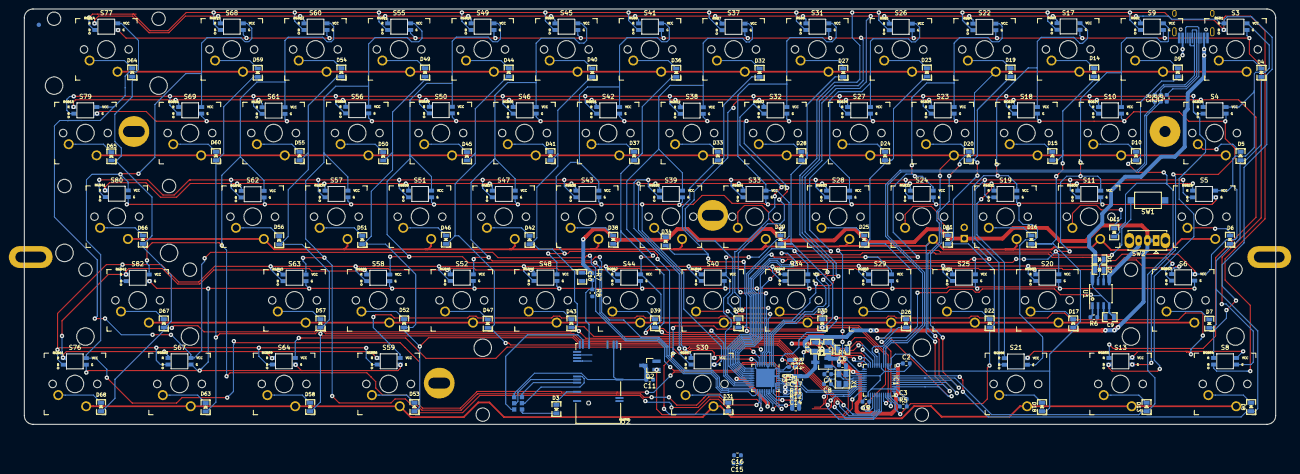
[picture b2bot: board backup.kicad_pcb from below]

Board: 2 copper layers, 285.0 x 94.6 mm, 245 parts (106 on the bottom side), 141 nets.

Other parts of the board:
C14: 104; R_0603_1608Metric
FID: FIDUCIAL
HOLE: VAL**; PKRHC
HOLE#2, HOLE#3, HOLE#4: VAL**; PKRH
HOLE#5, HOLE#6: VAL**; PKRHSL
MXST: VAL**; MXST
MXST#2, MXST#3, MXST#4, MXST#5, MXST#6, MXST#7, MXST#8, MXST#9, MXST#10: VAL**; MXST
P1: CONN_3X2; Jumper-UserFriendly
R11: 10k; R_0603_1608Metric

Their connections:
/DFU: P1.5; also elsewhere on the board
/DIO_RST: P1.3; also elsewhere on the board
/FACRST: P1.4; also elsewhere on the board
/SWCLK: P1.2; also elsewhere on the board
GND: C14.2, P1.6; also elsewhere on the board
unnamed 67: P1.1; also elsewhere on the board
unnamed 68: C14.1, R11.2; also elsewhere on the board

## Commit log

2019-12-02 2ndGen First version
2019-12-05 Fix Bugs
2020-02-23 2nd Gen BT-Keyboard
2020-02-23 1st Gen BT-Keyboard
2020-02-23 default GH60 Keyboard
